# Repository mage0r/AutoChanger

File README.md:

AutoChanger - A Knitting Machine Auto Colour Changer to replace a Brother KRC-900
=============

This project was designed to provide a lower cost replacement for the commercial auto colour changer available from Brother for their 1980's electronic knitting machines.

How to use your AutoChanger
============

Thanks for purchasing or building your own AutoChanger.  I've put together a page of all the different features for you to try.

It is highly recommended you upgrade your AutoChanger firmware to the latest.  The current latest is v4.3.3

[How to Upgrade Your AutoChanger Firmware](https://github.com/mage0r/AutoChanger/wiki/How%E2%80%90to%E2%80%90upgrade)

[How to Use Your AutoChanger](https://github.com/mage0r/AutoChanger/wiki/How-to-use-Firmware-Version-4.3)

[Still using Version-3.9?  Check it out here](https://github.com/mage0r/AutoChanger/wiki/How-to-use-Firmware-Version-3.9)

Where did this come from?
============

You can read about the progress of this design at the following links:

[Building a better colour changer - Part 1 - Designing Hardware](https://github.com/mage0r/AutoChanger/wiki/Building-a-better-Colour-Changer-%E2%80%93-Part-1-%E2%80%93-Designing-hardware)

[Building a better colour changer - Part 2 - Firing the lasers](https://github.com/mage0r/AutoChanger/wiki/Building-a-better-Colour-Changer-%E2%80%93-Part-2-%E2%80%93-Firing-the-Lasers)

[Building a Better Colour Changer  Interlude  The KRC-1000E](https://github.com/mage0r/AutoChanger/wiki/Building-a-Better-Colour-Changer-%E2%80%93-Interlude-%E2%80%93-The-KRC%E2%80%901000E)

[Building a Better Colour Changer  Part 3  Revising the design](https://github.com/mage0r/AutoChanger/wiki/Building-a-Better-Colour-Changer-%E2%80%93-Part-3-%E2%80%93-Revising-the-design)

For the sake of completeness, the early versions of this project are described at [Hardware Version 1.0 to 2.0]https://github.com/mage0r/AutoChanger/wiki/Hardware-Version-1.0-to-2.0)

Version 2.0 to 3.0 was TinyPico Based.  You can read about it at [Hardware Version 2.0 to 3.0](https://github.com/mage0r/AutoChanger/wiki/Hardware-Version-2.0-to-3.0)

Version 3.0 is a whole new build using an ESP32s3.  You can read about it at [Hardware Version 3.0](https://github.com/mage0r/AutoChanger/wiki/Hardware-Version-3.0)

CREDITS
------------

This project was designed in 2017 by John and Sarah Spencer
 - [John Spencer](https://github.com/mage0r)
 - [Sarah Spencer](https://github.com/chixor)

Check us out at [Heart Of Pluto](http://heartofpluto.co)

Made at hackmelbourne.org!

SPECIAL THANKS
------------

To the HackMelbourne (CCHS, http://hackmelbourne.org) community of Melbourne, Australia.

To all other open-source developers whose countless hours supported every other aspect of this design.

DISTRIBUTION
------------
The specific terms of distribution of this project are governed by the
license referenced below. Please contact the copyright owner if you wish to modify the board for distribution. Please utilize this design for personal or research projects. Please acknowledge all contributors.

LICENSE
-------
Licensed under the TAPR Open Hardware License (www.tapr.org/OHL).
The "license" sub-folder also contains a copy of this license in plain text format.

Copyright John Spencer, Sarah Spencer, 2017

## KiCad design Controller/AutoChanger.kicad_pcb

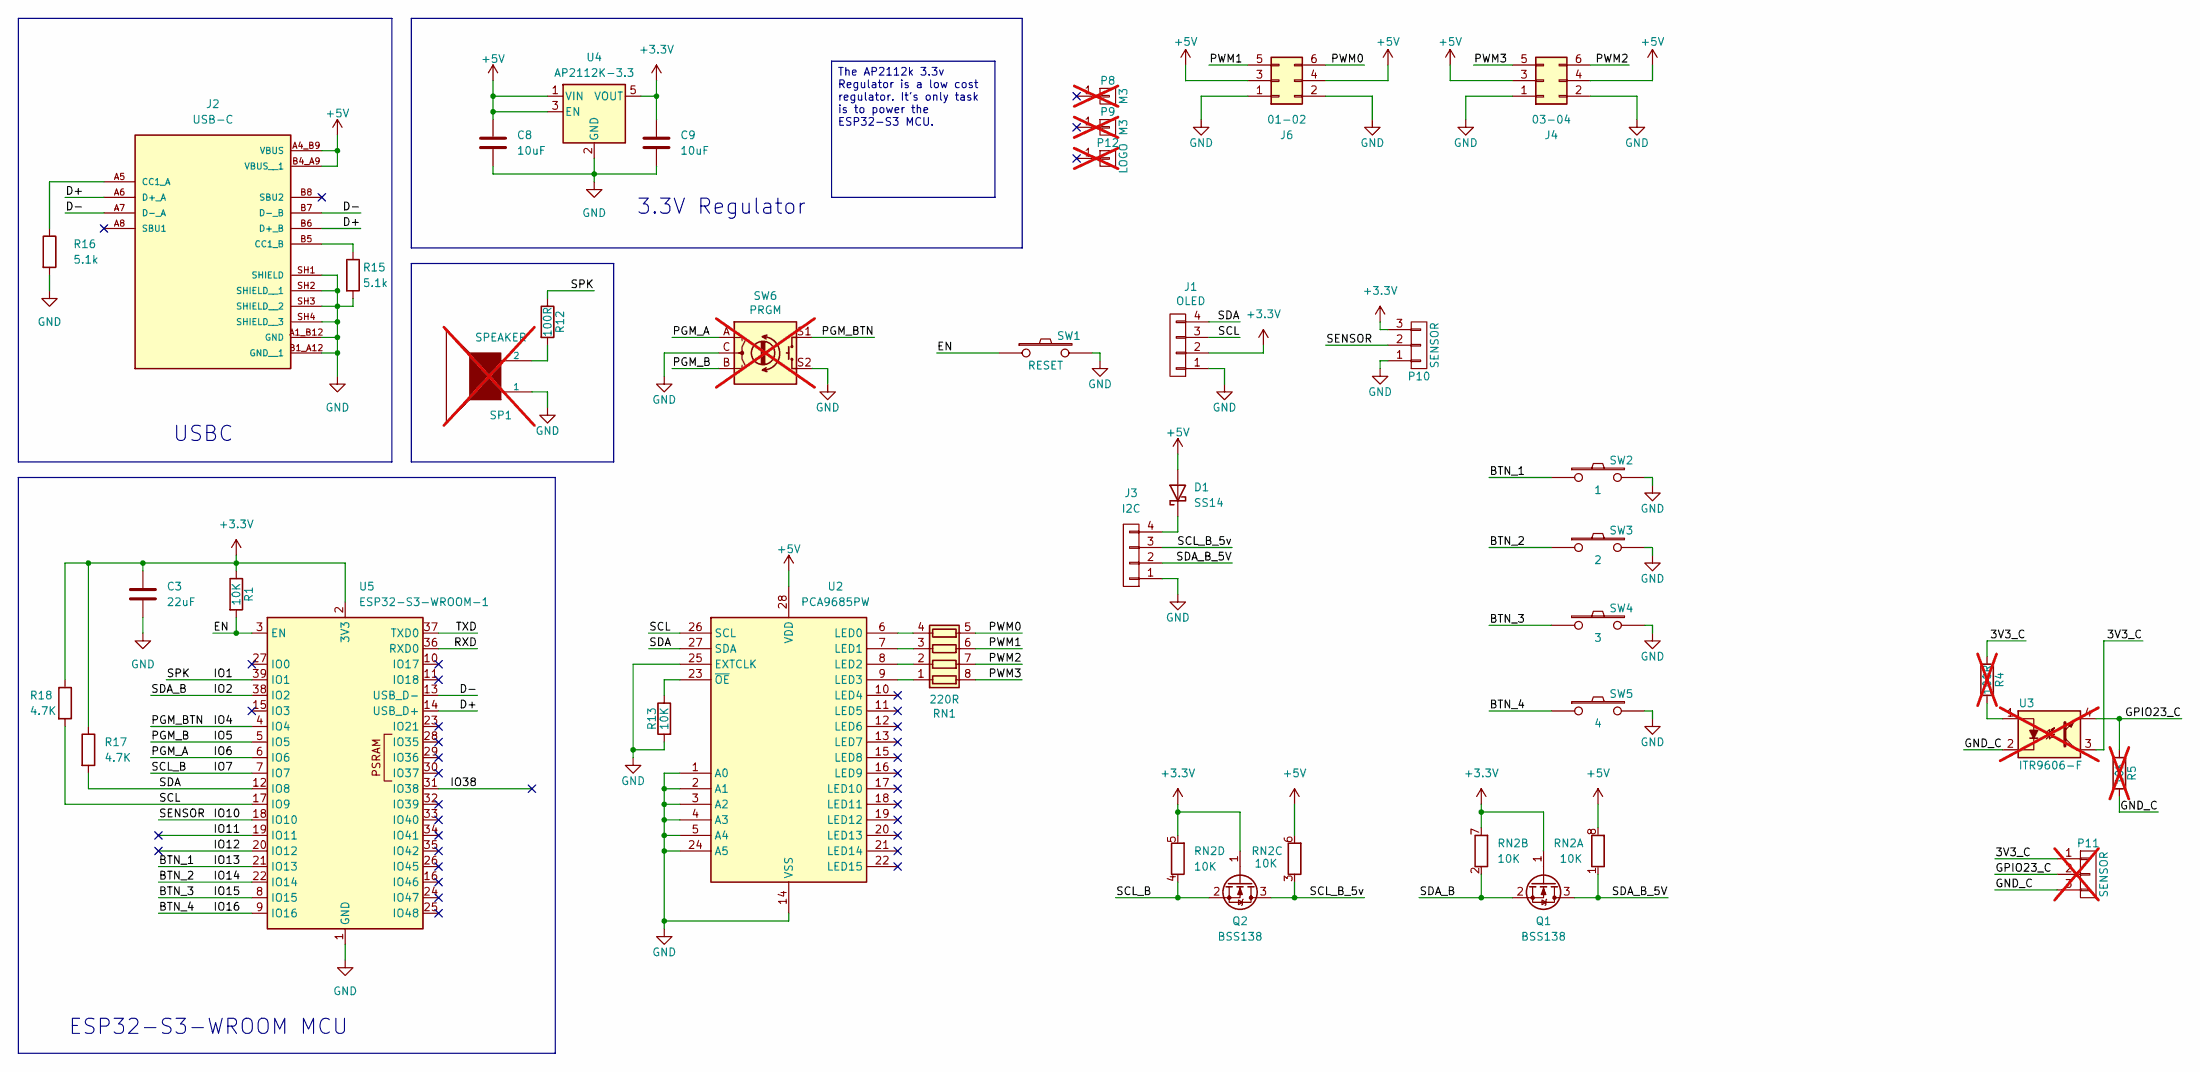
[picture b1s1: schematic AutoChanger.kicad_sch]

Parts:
C3: 22uF; C_0603_1608Metric; LCSC C59461
C8, C9: 10uF; C_0603_1608Metric; LCSC C19702
D1: SS14; D_SMA; LCSC C2480
J1: OLED; 0.91 OLED; LCSC C5248081
J2: USB-C; AMPHENOL_12402012E212A; PARTREV 4; LCSC C5150972
J3: I2C; CONN-SMD_PH2.0MM-4P-WT; LCSC C53055420
J4: 03-04; HDR-SMD_6P-P2.54-V-M-R2-C3-LS7.5-2; LCSC C3294461
J6: 01-02; HDR-SMD_6P-P2.54-V-M-R2-C3-LS7.5-2; LCSC C3294461
P8, P9: M3; MountingHole_3.2mm_M3; not fitted
P10: SENSOR; CONN-SMD_PH2.0MM-3P-WT; LCSC C53055419
P11: SENSOR; PinHeader_1x03_P2.54mm_Vertical; not fitted
P12: LOGO; logo; not fitted
Q1, Q2: BSS138; SOT-23; LCSC C8490
R1, R13: 10K; R_0603_1608Metric_Pad0.98x0.95mm_HandSolder; LCSC C25804
R4: 100R; R_0603_1608Metric_Pad0.98x0.95mm_HandSolder; LCSC C22775; not fitted
R5: 10K; R_0603_1608Metric_Pad0.98x0.95mm_HandSolder; LCSC C25804; not fitted
R12: 100R; R_0603_1608Metric_Pad0.98x0.95mm_HandSolder; LCSC C22775
R15, R16: 5.1k; R_0603_1608Metric_Pad0.98x0.95mm_HandSolder; LCSC C23186
R17, R18: 4.7K; R_0603_1608Metric_Pad0.98x0.95mm_HandSolder; LCSC C23162
RN1: 220R; R_Array_Concave_4x0603; LCSC C29719
RN2: 10K; R_Array_Convex_4x0603; LCSC C29718
SP1: SPEAKER; Buzzer_12x9.5RM7.6; not fitted
SW1: RESET; SW_SPST_PTS645Sx43SMTR92; LCSC C557614
SW2: 1; SW_SPST_PTS645Sx43SMTR92; LCSC C53202676
SW3: 2; SW_SPST_PTS645Sx43SMTR92; LCSC C53202676
SW4: 3; SW_SPST_PTS645Sx43SMTR92; LCSC C53202676
SW5: 4; SW_SPST_PTS645Sx43SMTR92; LCSC C53202676
SW6: PRGM; RotaryEncoder_Alps_EC12E-Switch_Vertical_H20mm; LCSC C470742; not fitted
U2: PCA9685PW; TSSOP-28_4.4x9.7mm_P0.65mm; LCSC C2678753
U3: ITR9606-F; ITR9606; not fitted
U4: AP2112K-3.3; SOT-23-5; LCSC C51118
U5: ESP32-S3-WROOM-1; LCSC C2913202

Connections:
+3.3V: C3.1, C9.1, J1.2, P10.3, Q1.1 (G), Q2.1 (G), R1.1, R17.1, R18.1, RN2.5 (R4.2), RN2.7 (R2.2), U4.5 (VOUT), U5.2 (3V3)
+5V: C8.1, D1.2 (A), J2.A4_B9 (VBUS), J2.B4_A9 (VBUS__1), J4.3, J4.4, J6.3, J6.4, RN2.6 (R3.2), RN2.8 (R1.2), U2.28 (VDD), U4.1 (VIN), U4.3 (EN)
/3V3_C: P11.1, R4.1, U3.3
/BTN_1: SW2.1, U5.21 (IO13)
/BTN_2: SW3.1, U5.22 (IO14)
/BTN_3: SW4.1, U5.8 (IO15)
/BTN_4: SW5.1, U5.9 (IO16)
/D+: J2.A6 (D+_A), J2.B6 (D+_B), U5.14 (USB_D+)
/D-: J2.A7 (D-_A), J2.B7 (D-_B), U5.13 (USB_D-)
/EN: R1.2, SW1.1, U5.3 (EN)
/GND_C: P11.3, R5.2, U3.2
/GPIO23_C: P11.2, R5.1, U3.4
/IO1: R12.1, U5.39 (IO1)
/IO2: Q1.2 (S), RN2.2 (R2.1), U5.38 (IO2)
/IO4: SW6.S1, U5.4 (IO4)
/IO5: SW6.B, U5.5 (IO5)
/IO6: SW6.A, U5.6 (IO6)
/IO7: Q2.2 (S), RN2.4 (R4.1), U5.7 (IO7)
/IO10: P10.2, U5.18 (IO10)
/IO11: U5.19 (IO11)
/IO12: U5.20 (IO12)
/IO38: U5.31 (IO38)
/PWM0: J6.6, RN1.5 (R4.2)
/PWM1: J6.5, RN1.6 (R3.2)
/PWM2: J4.6, RN1.7 (R2.2)
/PWM3: J4.5, RN1.8 (R1.2)
/RXD: U5.36 (RXD0)
/SCL: J1.3, R18.2, U2.26 (SCL), U5.17 (IO9)
/SCL_B_5v: J3.3, Q2.3 (D), RN2.3 (R3.1)
/SDA: J1.4, R17.2, U2.27 (SDA), U5.12 (IO8)
/SDA_B_5V: J3.2, Q1.3 (D), RN2.1 (R1.1)
/TXD: U5.37 (TXD0)
GND: C3.2, C8.2, C9.2, J1.1, J2.A1_B12 (GND), J2.B1_A12 (GND__1), J2.SH1 (SHIELD), J2.SH2 (SHIELD__1), J2.SH3 (SHIELD__2), J2.SH4 (SHIELD__3), J3.1, J4.1, J4.2, J6.1, J6.2, P10.1, R13.2, R15.2, R16.2, SP1.1, SW1.2, SW2.2, SW3.2, SW4.2, SW5.2, SW6.C, SW6.S2, U2.1 (A0), U2.2 (A1), U2.3 (A2), U2.4 (A3), U2.5 (A4), U2.14 (VSS), U2.24 (A5), U2.25 (EXTCLK), U4.2 (GND), U5.1 (GND), U5.40 (GND), U5.41 (GND)
unnamed: D1.1 (K), J3.4
unnamed: J2.A5 (CC1_A), R16.1
unnamed: J2.B5 (CC1_B), R15.1
unnamed: R4.2, U3.1
unnamed: R12.2, SP1.2
unnamed: RN1.1 (R1.1), U2.9 (LED3)
unnamed: RN1.2 (R2.1), U2.8 (LED2)
unnamed: RN1.3 (R3.1), U2.7 (LED1)
unnamed: RN1.4 (R4.1), U2.6 (LED0)
unnamed: R13.1, U2.23 (~OE)

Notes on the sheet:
USBC
ESP32-S3-WROOM MCU
3.3V Regulator
The AP2112k 3.3v Regulator is a low cost regulator. It's only task is to power the ESP32-S3 MCU.

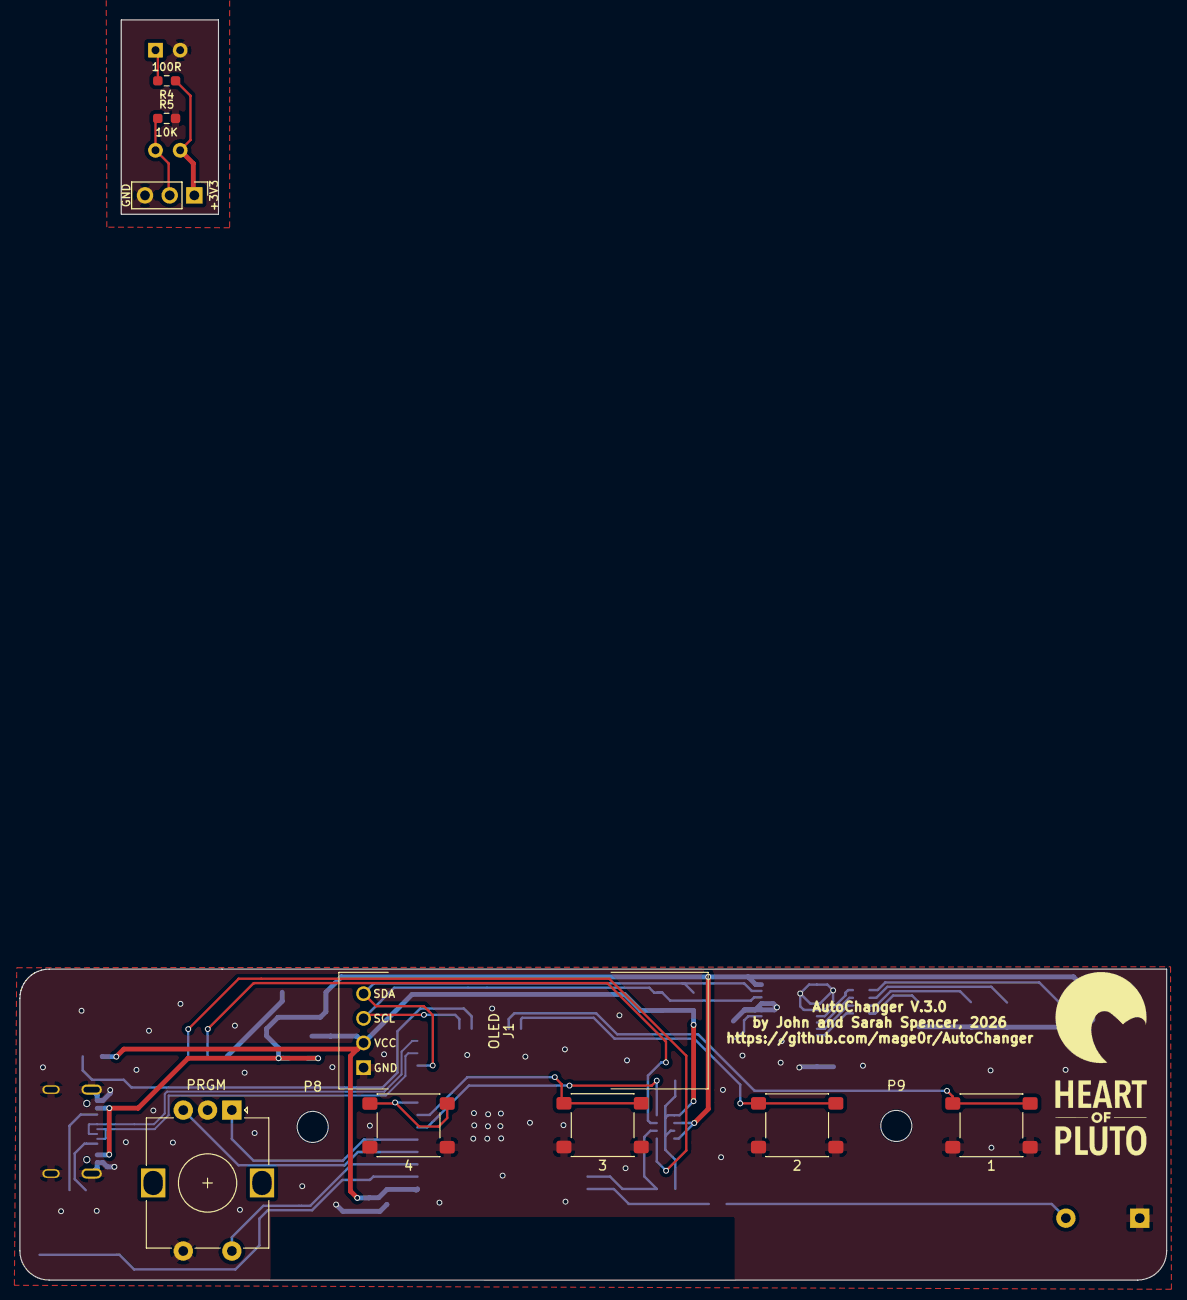
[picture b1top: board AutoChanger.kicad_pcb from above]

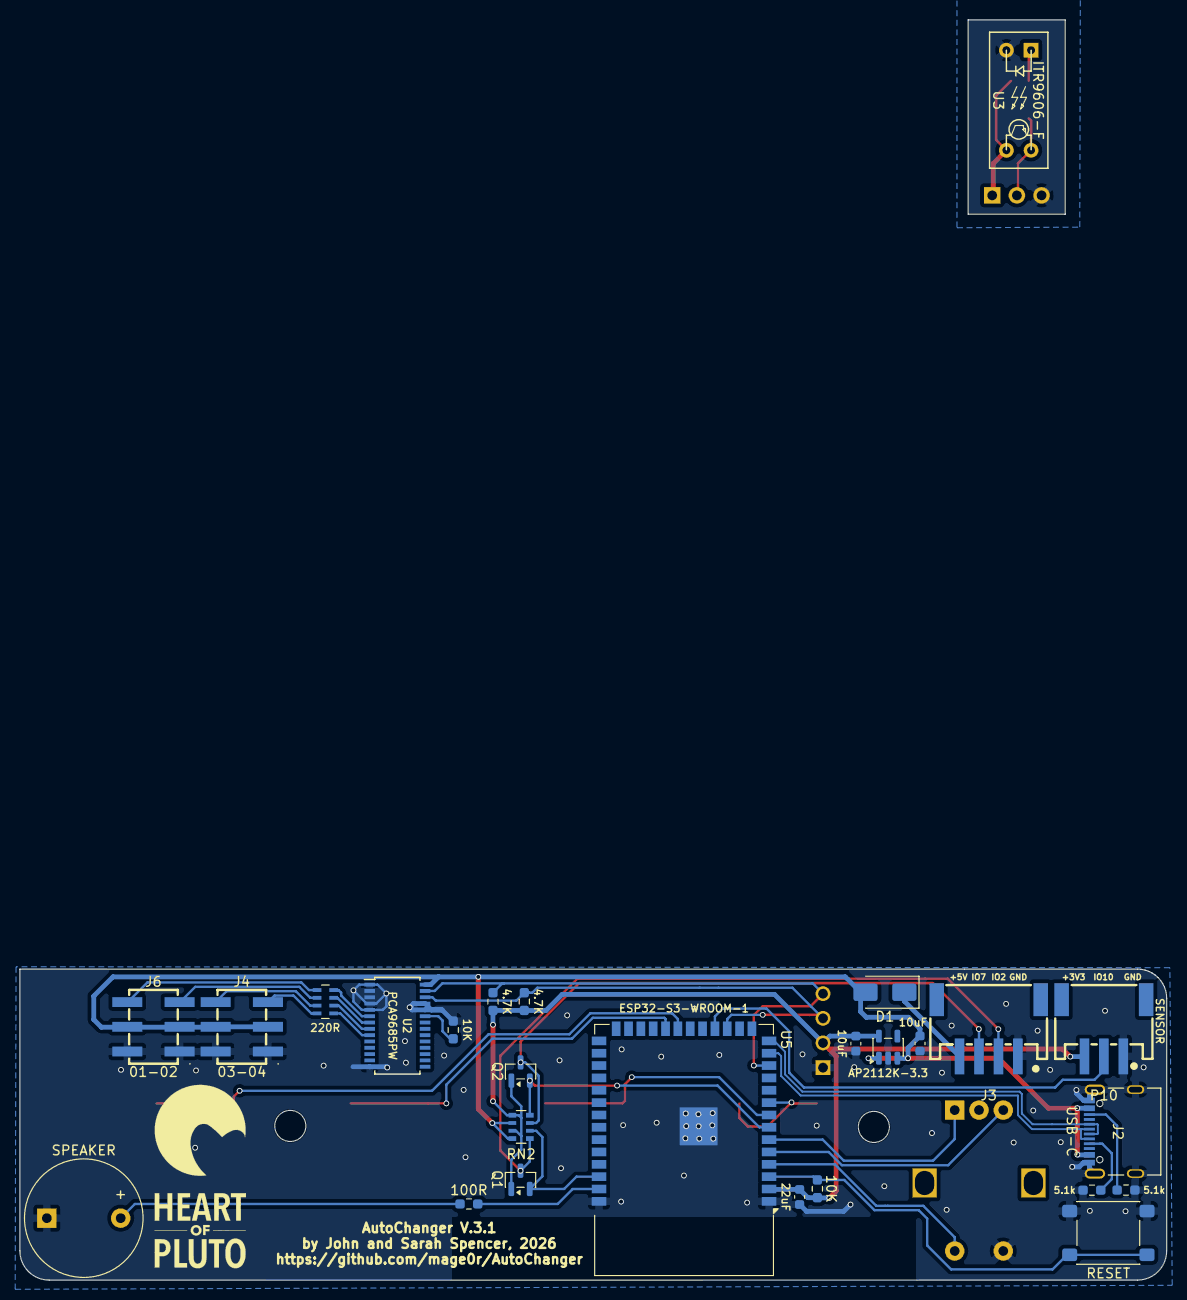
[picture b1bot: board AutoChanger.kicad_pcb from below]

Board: 2 copper layers, 118.0 x 129.7 mm, 39 parts (27 on the bottom side), 38 nets.

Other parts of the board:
P12#2: LOGO; logo

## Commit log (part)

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2019-11-06 I'm sure there's value here.
2019-11-06 Added basic OLED stuff
2023-10-05 In the progress of incorporating a Webserver to configure the changer
2023-10-05 Mounting hardware
2023-10-05 Tinypico compatible controller
2023-10-05 Updated for Kicad 7.0
2025-11-03 Kicking off another round of development
2025-11-03 V3.8 working
    Oh boy, broken code there.
    Version 4 Software isn't complete.
    Version 3 Software should work.
2026-06-29 Adding images from blog posts
    updating repo to have old blog post content here too
2026-06-29 Second page Images
2026-06-29 Interlude photos
2026-06-29 3rd set of images and updated links
2026-06-29 updated image for interlude
2026-06-29 Version 2.0 Hardware image
